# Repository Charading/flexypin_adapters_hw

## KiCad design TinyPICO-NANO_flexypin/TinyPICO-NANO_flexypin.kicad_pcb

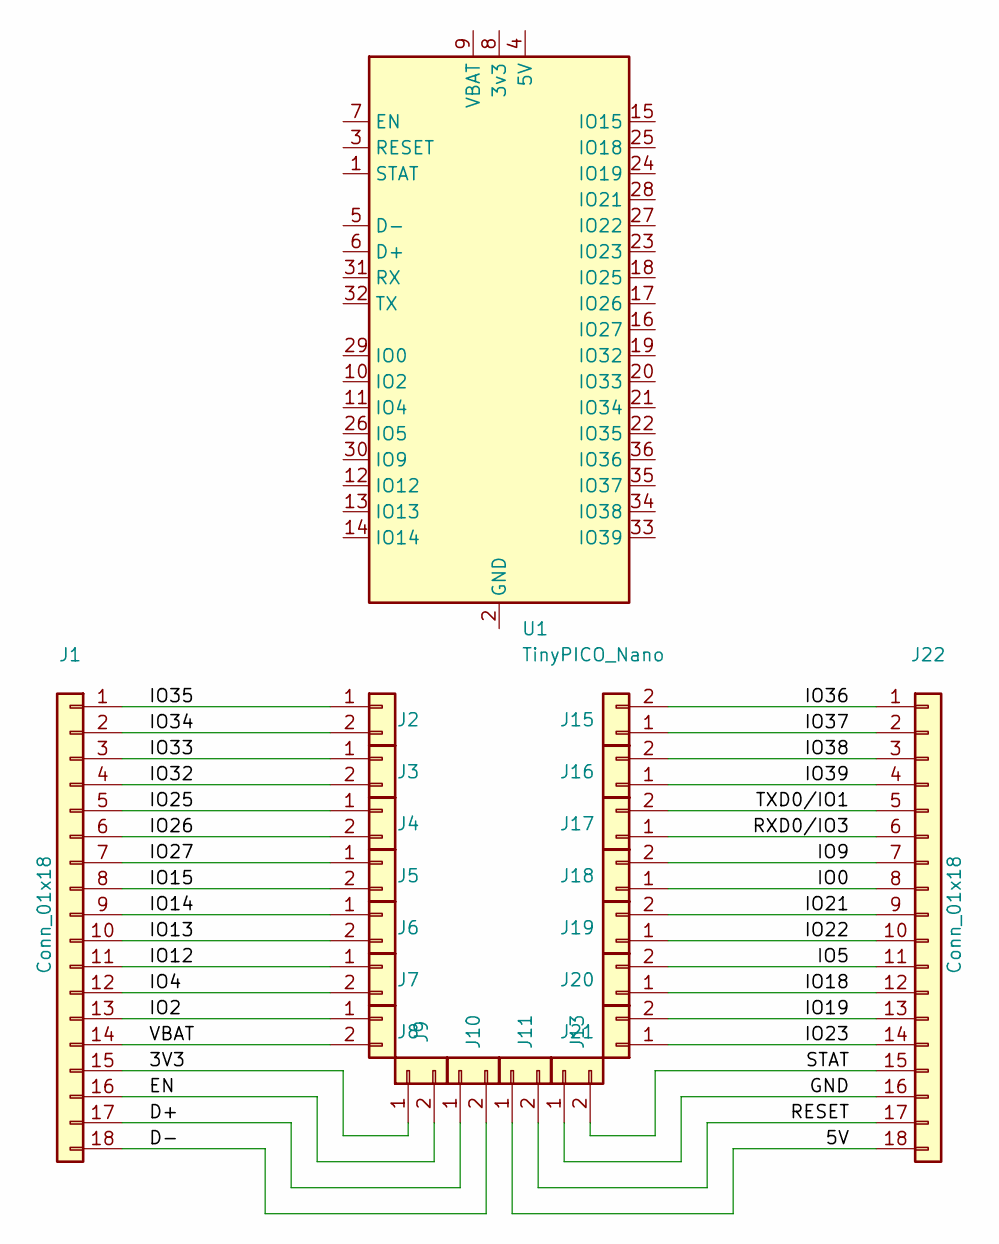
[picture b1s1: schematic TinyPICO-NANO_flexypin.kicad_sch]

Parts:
J1, J22: Conn_01x18; PinHeader_1x18_P2.54mm_Vertical
J2, J3, J4, J5, J6, J7, J8, J9, J10, J11, J13, J15, J16, J17, J18, J19, J20, J21: Conn_01x02; FlexyPin_1x02_P1.27mm
U1: TinyPICO_Nano

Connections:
/3V3: J1.15, J9.1
/5V: J11.1, J22.18
/D+: J1.17, J10.1
/D-: J1.18, J10.2
/EN: J1.16, J9.2
/GND: J13.1, J22.16
/IO0: J18.1, J22.8
/IO2: J1.13, J8.1
/IO4: J1.12, J7.2
/IO5: J20.2, J22.11
/IO9: J18.2, J22.7
/IO12: J1.11, J7.1
/IO13: J1.10, J6.2
/IO14: J1.9, J6.1
/IO15: J1.8, J5.2
/IO18: J20.1, J22.12
/IO19: J21.2, J22.13
/IO21: J19.2, J22.9
/IO22: J19.1, J22.10
/IO23: J21.1, J22.14
/IO25: J1.5, J4.1
/IO26: J1.6, J4.2
/IO27: J1.7, J5.1
/IO32: J1.4, J3.2
/IO33: J1.3, J3.1
/IO34: J1.2, J2.2
/IO35: J1.1, J2.1
/IO36: J15.2, J22.1
/IO37: J15.1, J22.2
/IO38: J16.2, J22.3
/IO39: J16.1, J22.4
/RESET: J11.2, J22.17
/RXD0/IO3: J17.1, J22.6
/STAT: J13.2, J22.15
/TXD0/IO1: J17.2, J22.5
/VBAT: J1.14, J8.2

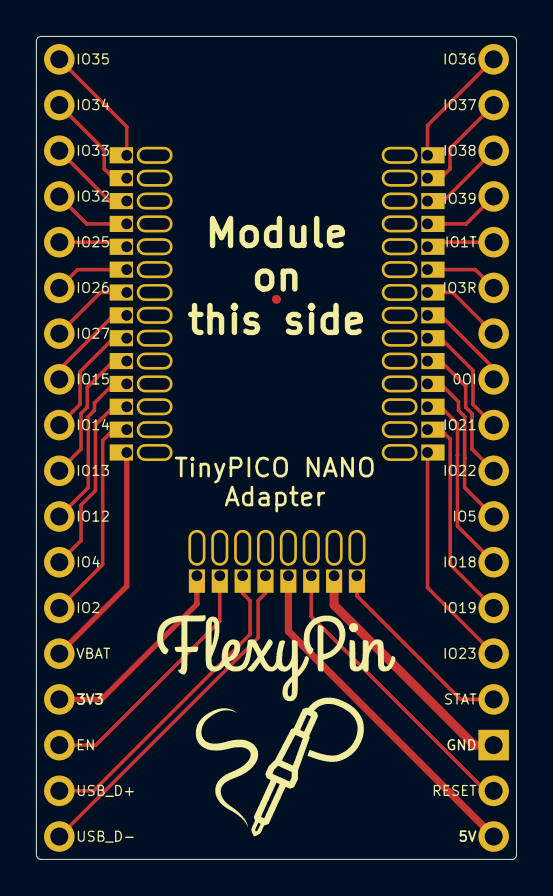
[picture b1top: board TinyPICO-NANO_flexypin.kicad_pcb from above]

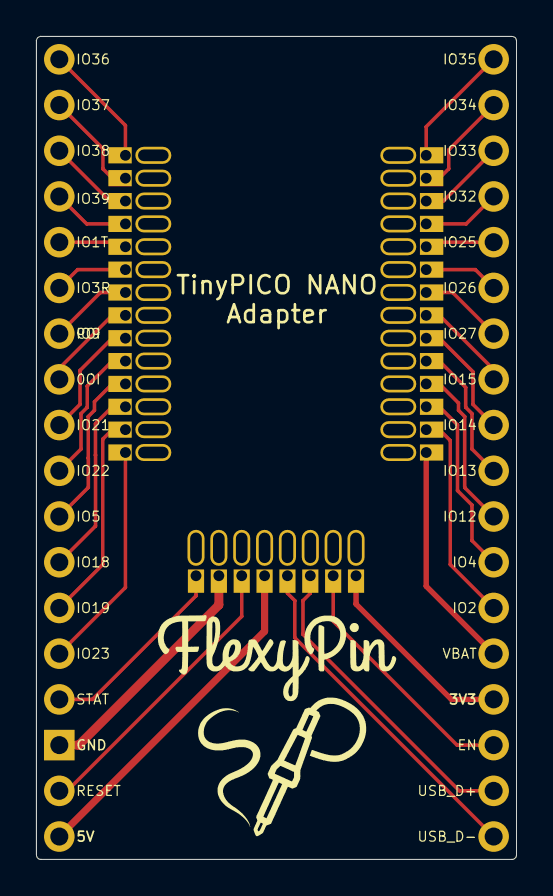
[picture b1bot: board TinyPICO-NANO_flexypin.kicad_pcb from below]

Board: 2 copper layers, 26.7 x 45.7 mm, 21 parts (2 on the bottom side), 36 nets.

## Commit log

2025-11-05 Add TinyPICO Nano V2 Adapter
2025-11-05 Fixed incorrect silkscreen labels
